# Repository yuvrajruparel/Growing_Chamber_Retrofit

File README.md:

# (De)Humidifer 6700

Project Structure

- `chamber-log/` contains the ESP32 firmware for collecting chamber data.
- `firmware/` will contain the final firmware for the machine (todo).
- `mycorrhizal/` PCB schematic (for use with KiCAD)
- `proto-dehumidifier/` contains arduino firmware for the 1st dehumidifier prototype
    - `tester/tester.ino` fan firmware for dehumidifier test cycles
- `assets (CAD)/` contains all the CAD files used.

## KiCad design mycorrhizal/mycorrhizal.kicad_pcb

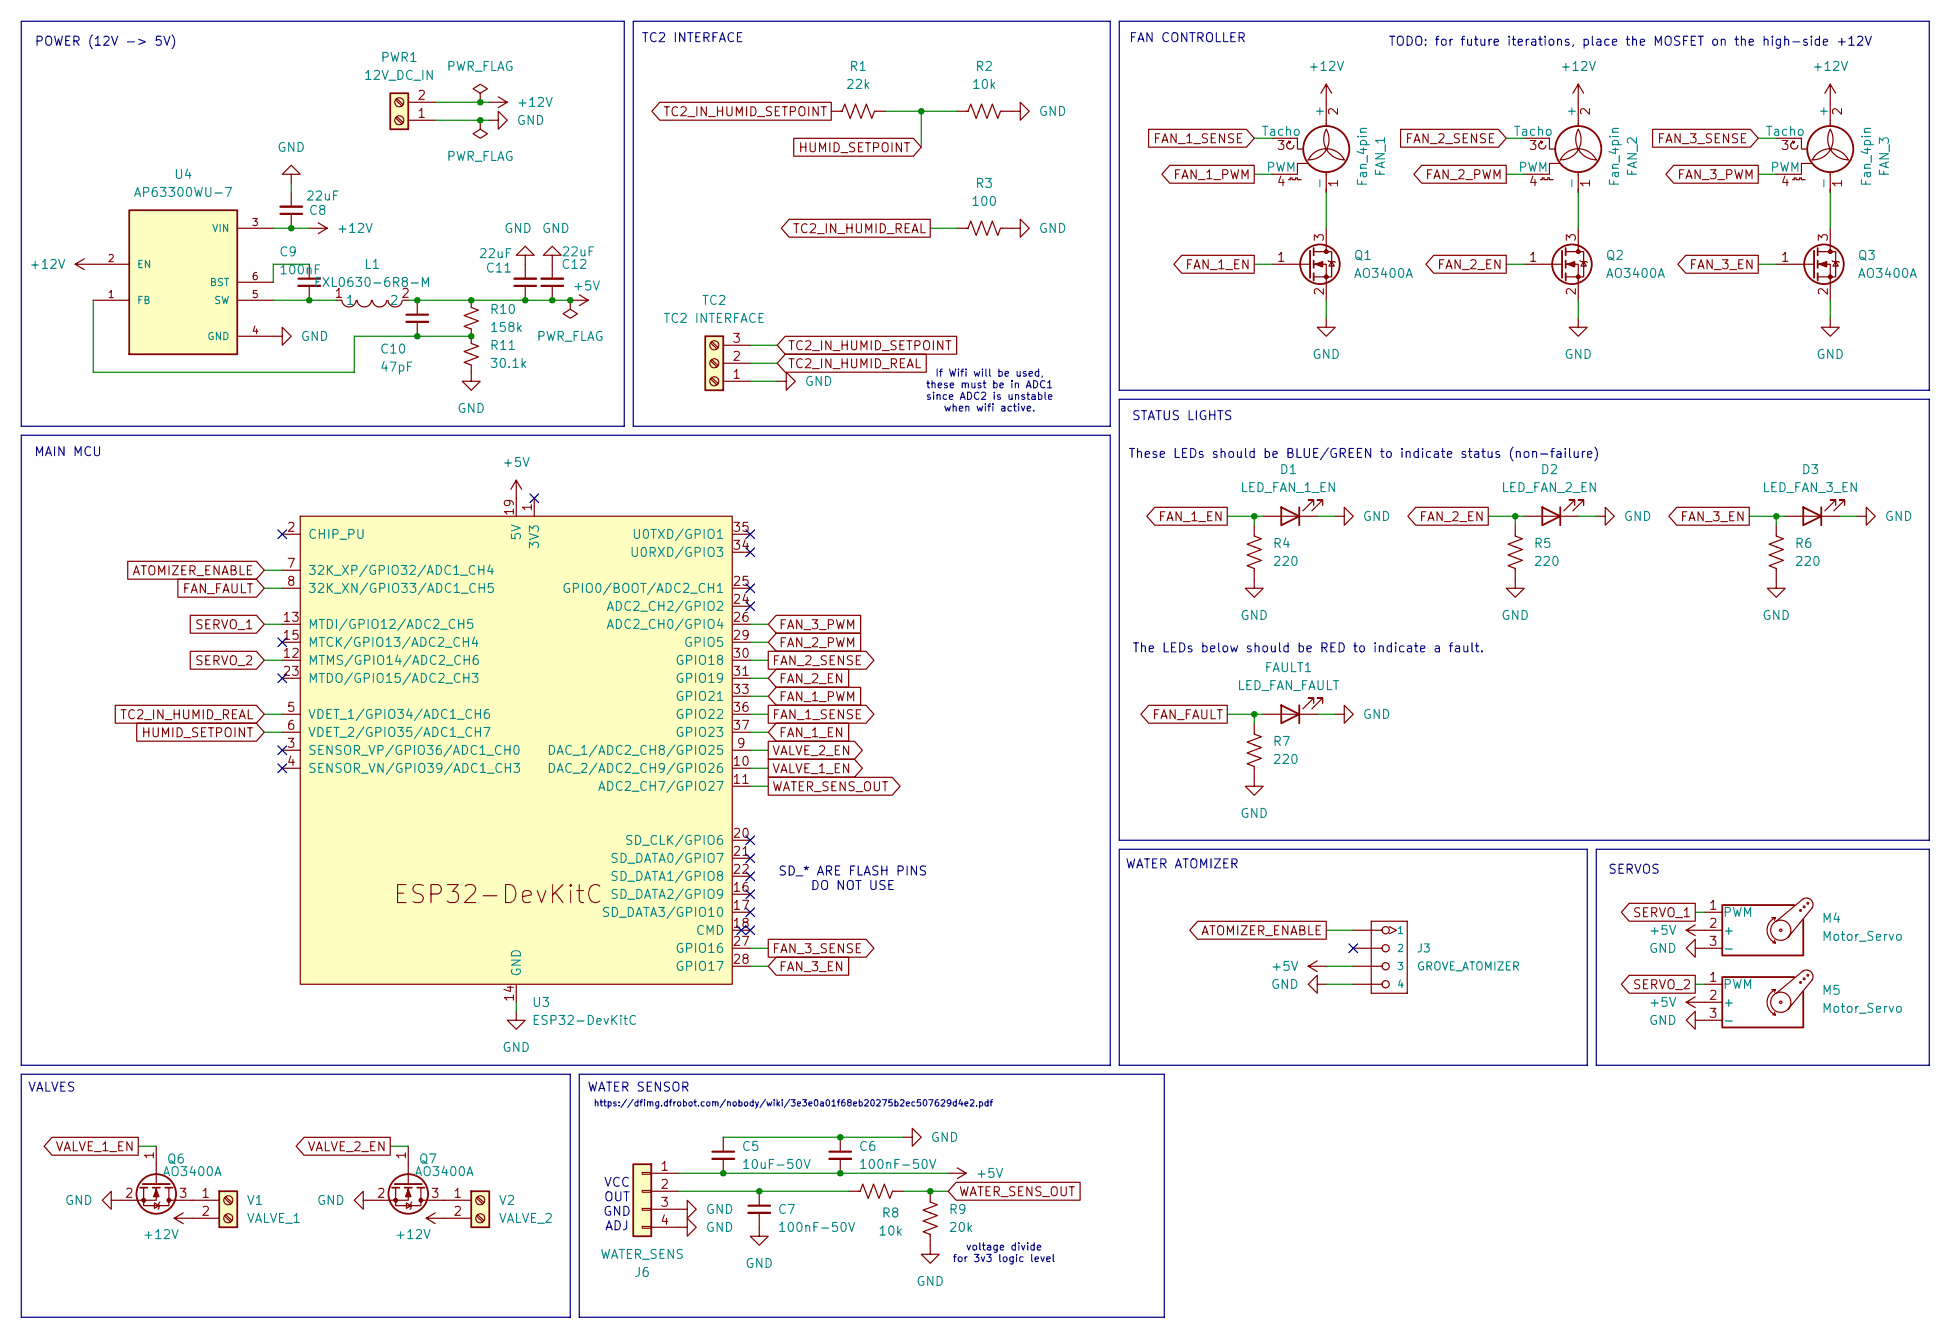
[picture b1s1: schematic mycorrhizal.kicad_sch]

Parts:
C5: 10uF-50V; C_0805_2012Metric_Pad1.18x1.45mm_HandSolder
C6, C7: 100nF-50V; C_0805_2012Metric_Pad1.18x1.45mm_HandSolder; LCSC C49678
C8, C11, C12: 22uF; C_1210_3225Metric_Pad1.33x2.70mm_HandSolder; LCSC C309062
C9: 100nF; C_0805_2012Metric_Pad1.18x1.45mm_HandSolder; LCSC C49678
C10: 47pF; C_0603_1608Metric_Pad1.08x0.95mm_HandSolder
D1: LED_FAN_1_EN; LED_0805_2012Metric_Pad1.15x1.40mm_HandSolder; LCSC C6457760
D2: LED_FAN_2_EN; LED_0805_2012Metric_Pad1.15x1.40mm_HandSolder; LCSC C6457760
D3: LED_FAN_3_EN; LED_0805_2012Metric_Pad1.15x1.40mm_HandSolder; LCSC C6457760
FAN_1, FAN_2, FAN_3: Fan_4pin; FanPinHeader_1x04_P2.54mm_Vertical; LCSC C240840
FAULT1: LED_FAN_FAULT; LED_0805_2012Metric_Pad1.15x1.40mm_HandSolder; LCSC C51933307
J3: GROVE_ATOMIZER; NS-Tech_Grove_1x04_P2mm_Vertical
J6: WATER_SENS; JST_XH_B4B-XH-A_1x04_P2.50mm_Vertical
L1: FXL0630-6R8-M; IND-SMD_L7.0-W6.6; LCSC Part C167221
M4, M5: Motor_Servo; PinHeader_1x03_P2.54mm_Vertical; LCSC C49257
PWR1: 12V_DC_IN; TerminalBlock_bornier-2_P5.08mm
Q1, Q2, Q3, Q6, Q7: AO3400A; SOT-23; LCSC C20917
R1: 22k; R_0805_2012Metric_Pad1.20x1.40mm_HandSolder
R2, R8: 10k; R_0805_2012Metric_Pad1.20x1.40mm_HandSolder
R3: 100; R_0805_2012Metric_Pad1.20x1.40mm_HandSolder
R4, R5, R6, R7: 220; R_0805_2012Metric_Pad1.20x1.40mm_HandSolder
R9: 20k; R_0805_2012Metric_Pad1.20x1.40mm_HandSolder
R10: 158k; R_0805_2012Metric_Pad1.20x1.40mm_HandSolder
R11: 30.1k; R_0805_2012Metric_Pad1.20x1.40mm_HandSolder
TC2: TC2 INTERFACE; TerminalBlock_bornier-3_P5.08mm
U3: ESP32-DevKitC
U4: AP63300WU-7; SOT95P280X100-6N; PARTREV 2020-04-24; LCSC C2158012
V1: VALVE_1; TerminalBlock_bornier-2_P5.08mm
V2: VALVE_2; TerminalBlock_bornier-2_P5.08mm

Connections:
+5V: C5.2, C6.2, C10.1, C11.1, C12.1, J3.3, J6.1, L1.2, M4.2 (+), M5.2 (+), R10.1, U3.19 (5V)
+12V: C8.1, FAN_1.2 (+), FAN_2.2 (+), FAN_3.2 (+), PWR1.2, U4.2 (EN), U4.3 (VIN), V1.2, V2.2
ATOMIZER_ENABLE: J3.1, U3.7 (32K_XP/GPIO32/ADC1_CH4)
FAN_1_EN: D1.2 (A), Q1.1 (G), R4.2, U3.37 (GPIO23)
FAN_1_PWM: FAN_1.4 (PWM), U3.33 (GPIO21)
FAN_1_SENSE: FAN_1.3 (Tacho), U3.36 (GPIO22)
FAN_2_EN: D2.2 (A), Q2.1 (G), R5.2, U3.31 (GPIO19)
FAN_2_PWM: FAN_2.4 (PWM), U3.29 (GPIO5)
FAN_2_SENSE: FAN_2.3 (Tacho), U3.30 (GPIO18)
FAN_3_EN: D3.2 (A), Q3.1 (G), R6.2, U3.28 (GPIO17)
FAN_3_PWM: FAN_3.4 (PWM), U3.26 (ADC2_CH0/GPIO4)
FAN_3_SENSE: FAN_3.3 (Tacho), U3.27 (GPIO16)
FAN_FAULT: FAULT1.2 (A), R7.2, U3.8 (32K_XN/GPIO33/ADC1_CH5)
GND: C5.1, C6.1, C7.2, C8.2, C11.2, C12.2, D1.1 (K), D2.1 (K), D3.1 (K), FAULT1.1 (K), J3.4, J6.3, J6.4, M4.3 (-), M5.3 (-), PWR1.1, Q1.2 (S), Q2.2 (S), Q3.2 (S), Q6.2 (S), Q7.2 (S), R2.2, R3.2, R4.1, R5.1, R6.1, R7.1, R9.2, R11.2, TC2.1, U3.14 (GND), U3.32 (GND), U3.38 (GND), U4.4 (GND)
HUMID_SETPOINT: R1.2, R2.1, U3.6 (VDET_2/GPIO35/ADC1_CH7)
unnamed: FAN_1.1 (-), Q1.3 (D)
unnamed: FAN_2.1 (-), Q2.3 (D)
unnamed: FAN_3.1 (-), Q3.3 (D)
unnamed: C7.1, J6.2, R8.2
unnamed: Q6.3 (D), V1.1
unnamed: Q7.3 (D), V2.1
unnamed: C9.1, U4.6 (BST)
unnamed: C10.2, R10.2, R11.1, U4.1 (FB)
unnamed: C9.2, L1.1, U4.5 (SW)
SERVO_1: M4.1 (PWM), U3.13 (MTDI/GPIO12/ADC2_CH5)
SERVO_2: M5.1 (PWM), U3.12 (MTMS/GPIO14/ADC2_CH6)
TC2_IN_HUMID_REAL: R3.1, TC2.2, U3.5 (VDET_1/GPIO34/ADC1_CH6)
TC2_IN_HUMID_SETPOINT: R1.1, TC2.3
VALVE_1_EN: Q6.1 (G), U3.10 (DAC_2/ADC2_CH9/GPIO26)
VALVE_2_EN: Q7.1 (G), U3.9 (DAC_1/ADC2_CH8/GPIO25)
WATER_SENS_OUT: R8.1, R9.1, U3.11 (ADC2_CH7/GPIO27)

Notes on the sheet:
https://dfimg.dfrobot.com/nobody/wiki/3e3e0a01f68eb20275b2ec507629d4e2.pdf
voltage divide for 3v3 logic level
WATER SENSOR
WATER ATOMIZER
FAN CONTROLLER
These LEDs should be BLUE/GREEN to indicate status (non-failure)
POWER (12V -> 5V)
SD_* ARE FLASH PINS DO NOT USE
STATUS LIGHTS
TC2 INTERFACE
The LEDs below should be RED to indicate a fault.
VCC OUT GND ADJ
TODO: for future iterations, place the MOSFET on the high-side +12V
SERVOS
VALVES
MAIN MCU
If Wifi will be used, these must be in ADC1 since ADC2 is unstable when wifi active.

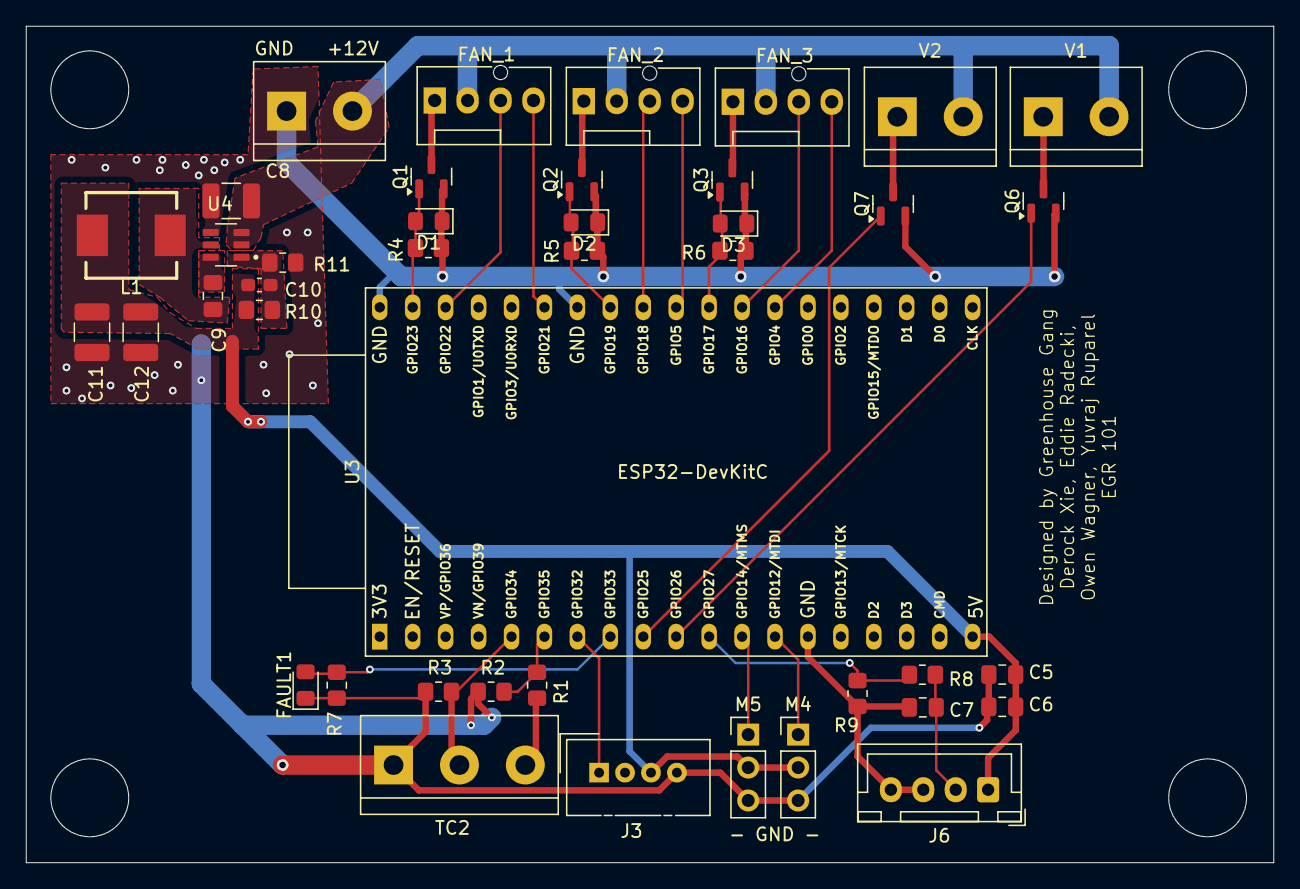
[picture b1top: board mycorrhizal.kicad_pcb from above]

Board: 2 copper layers, 96.2 x 64.5 mm, 42 parts (0 on the bottom side), 31 nets.
